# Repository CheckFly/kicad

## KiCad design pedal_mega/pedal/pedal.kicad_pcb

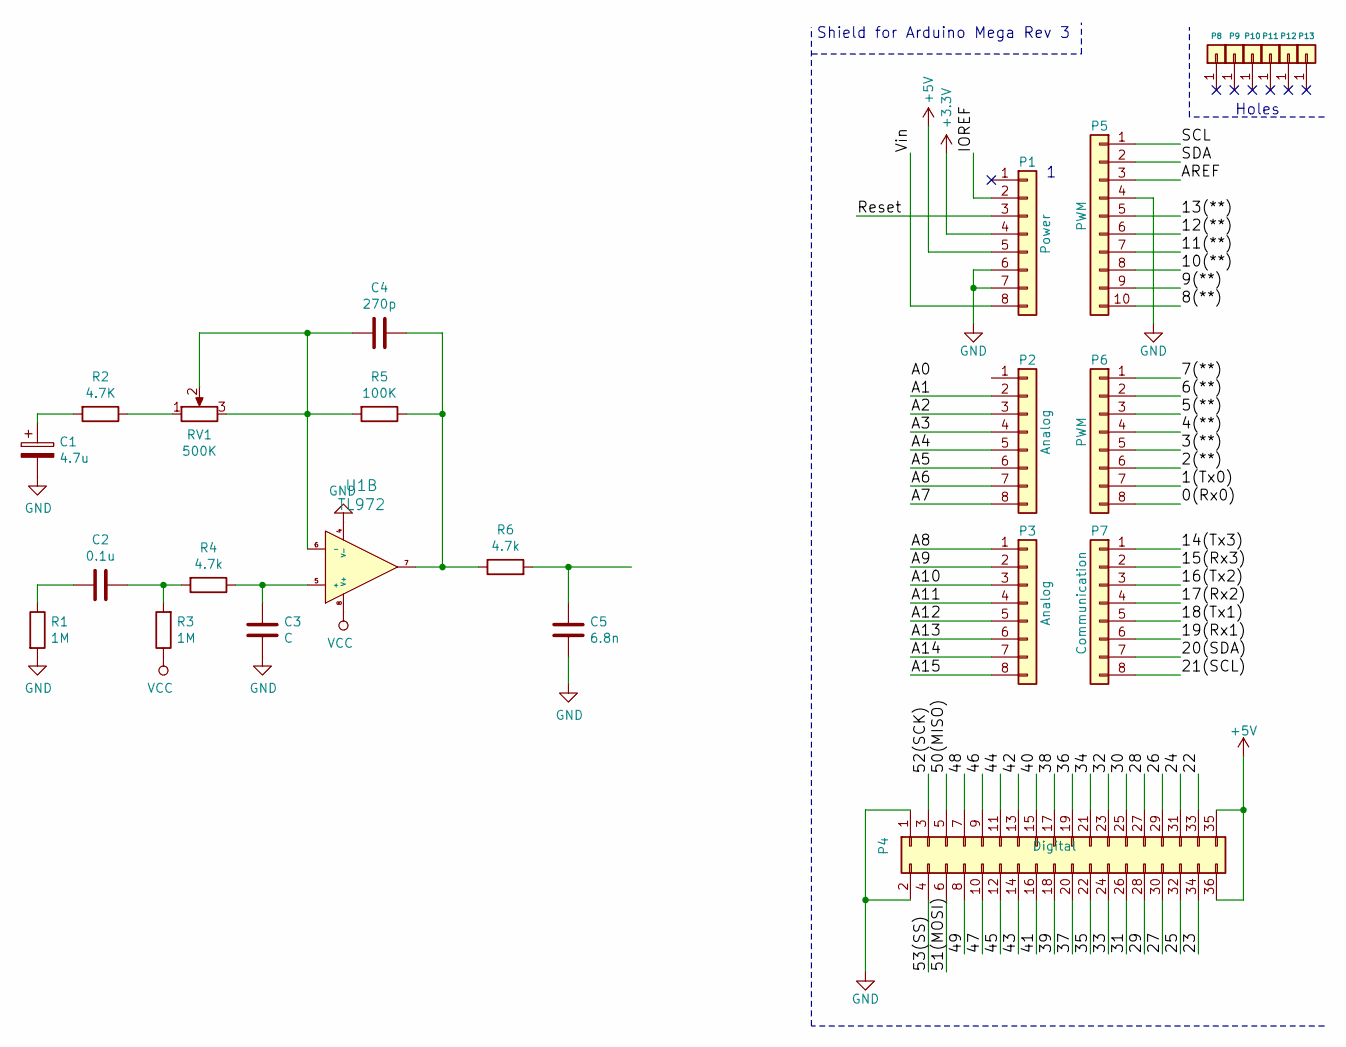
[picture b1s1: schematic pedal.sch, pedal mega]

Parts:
C1: 4.7u; CP_Radial_D10.0mm_P5.00mm
C2: 0.1u; C_Disc_D7.0mm_W2.5mm_P5.00mm
C3: C; C_Disc_D7.0mm_W2.5mm_P5.00mm
C4: 270p; CP_Radial_D10.0mm_P5.00mm
C5: 6.8n; CP_Radial_D10.0mm_P5.00mm
P1: Power; Socket_Strip_Arduino_1x08
P2, P3: Analog; Socket_Strip_Arduino_1x08
P4: Digital; Socket_Strip_Arduino_2x18
P5: PWM; Socket_Strip_Arduino_1x10
P6: PWM; Socket_Strip_Arduino_1x08
P7: Communication; Socket_Strip_Arduino_1x08
P8, P9, P10, P11, P12, P13: CONN_01X01; Arduino_1pin
R1, R3: 1M; R_Axial_DIN0207_L6.3mm_D2.5mm_P10.16mm_Horizontal
R2: 4.7K; R_Axial_DIN0207_L6.3mm_D2.5mm_P10.16mm_Horizontal
R4, R6: 4.7k; R_Axial_DIN0207_L6.3mm_D2.5mm_P10.16mm_Horizontal
R5: 100K; R_Axial_DIN0207_L6.3mm_D2.5mm_P10.16mm_Horizontal
RV1: 500K; Potentiometer_Vishay_T73YP_Vertical
U1: TL972; DIP-8_W7.62mm

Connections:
+3V3: P1.4
+5V: P1.5, P4.35, P4.36
/0(Rx0): P6.8
/1(Tx0): P6.7
/2(**): P6.6
/3(**): P6.5
/4(**): P6.4
/5(**): P6.3
/6(**): P6.2
/7(**): P6.1
/8(**): P5.10
/9(**): P5.9
/10(**): P5.8
/11(**): P5.7
/12(**): P5.6
/13(**): P5.5
/14(Tx3): P7.1
/15(Rx3): P7.2
/16(Tx2): P7.3
/17(Rx2): P7.4
/18(Tx1): P7.5
/19(Rx1): P7.6
/20(SDA): P7.7
/21(SCL): P7.8
/22: P4.33
/23: P4.34
/24: P4.31
/25: P4.32
/26: P4.29
/27: P4.30
/28: P4.27
/29: P4.28
/30: P4.25
/31: P4.26
/32: P4.23
/33: P4.24
/34: P4.21
/35: P4.22
/36: P4.19
/37: P4.20
/38: P4.17
/39: P4.18
/40: P4.15
/41: P4.16
/42: P4.13
/43: P4.14
/44: P4.11
/45: P4.12
/46: P4.9
/47: P4.10
/48: P4.7
/49: P4.8
/50(MISO): P4.5
/51(MOSI): P4.6
/52(SCK): P4.3
/53(SS): P4.4
/A1: P2.2
/A2: P2.3
/A3: P2.4
/A4: P2.5
/A5: P2.6
/A6: P2.7
/A7: P2.8
/A8: P3.1
/A9: P3.2
/A10: P3.3
/A11: P3.4
/A12: P3.5
/A13: P3.6
/A14: P3.7
/A15: P3.8
/AREF: P5.3
/IOREF: P1.2
/Reset: P1.3
/SCL: P5.1
/SDA: P5.2
/Vin: P1.8
GND: C1.2, C3.2, C5.2, P1.6, P1.7, P4.1, P4.2, P5.4, R1.2, U1.4 (V-)
unnamed: C1.1, R2.2
unnamed: C2.1, R3.2, R4.2
unnamed: C2.2, R1.1
unnamed: C3.1, R4.1, U1.5 (+)
unnamed: C4.1, R5.1, R6.1, U1.7
unnamed: C4.2, R5.2, RV1.2, RV1.3, U1.6 (-)
unnamed: C5.1, R6.2
unnamed: R2.1, RV1.1
VCC: R3.1, U1.8 (V+)

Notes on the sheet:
Shield for Arduino Mega Rev 3
Holes

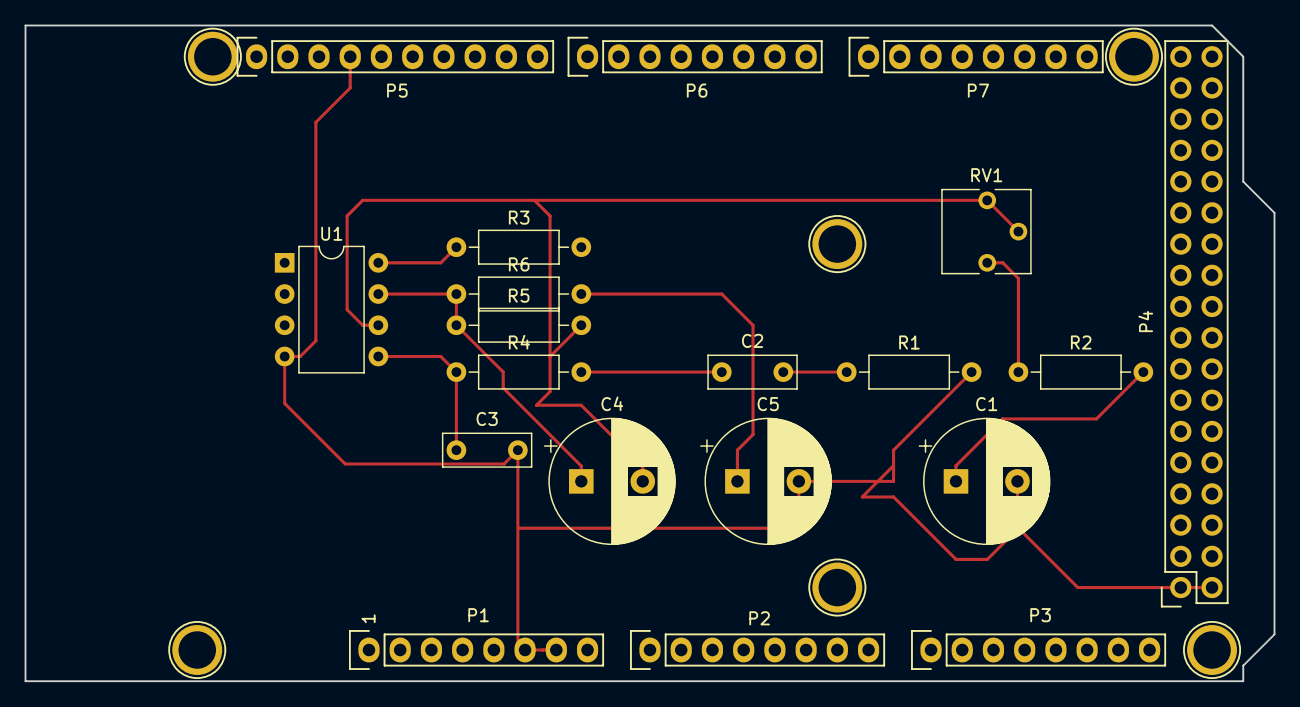
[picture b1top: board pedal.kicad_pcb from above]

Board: 2 copper layers, 101.6 x 53.3 mm, 26 parts (0 on the bottom side), 11 nets.

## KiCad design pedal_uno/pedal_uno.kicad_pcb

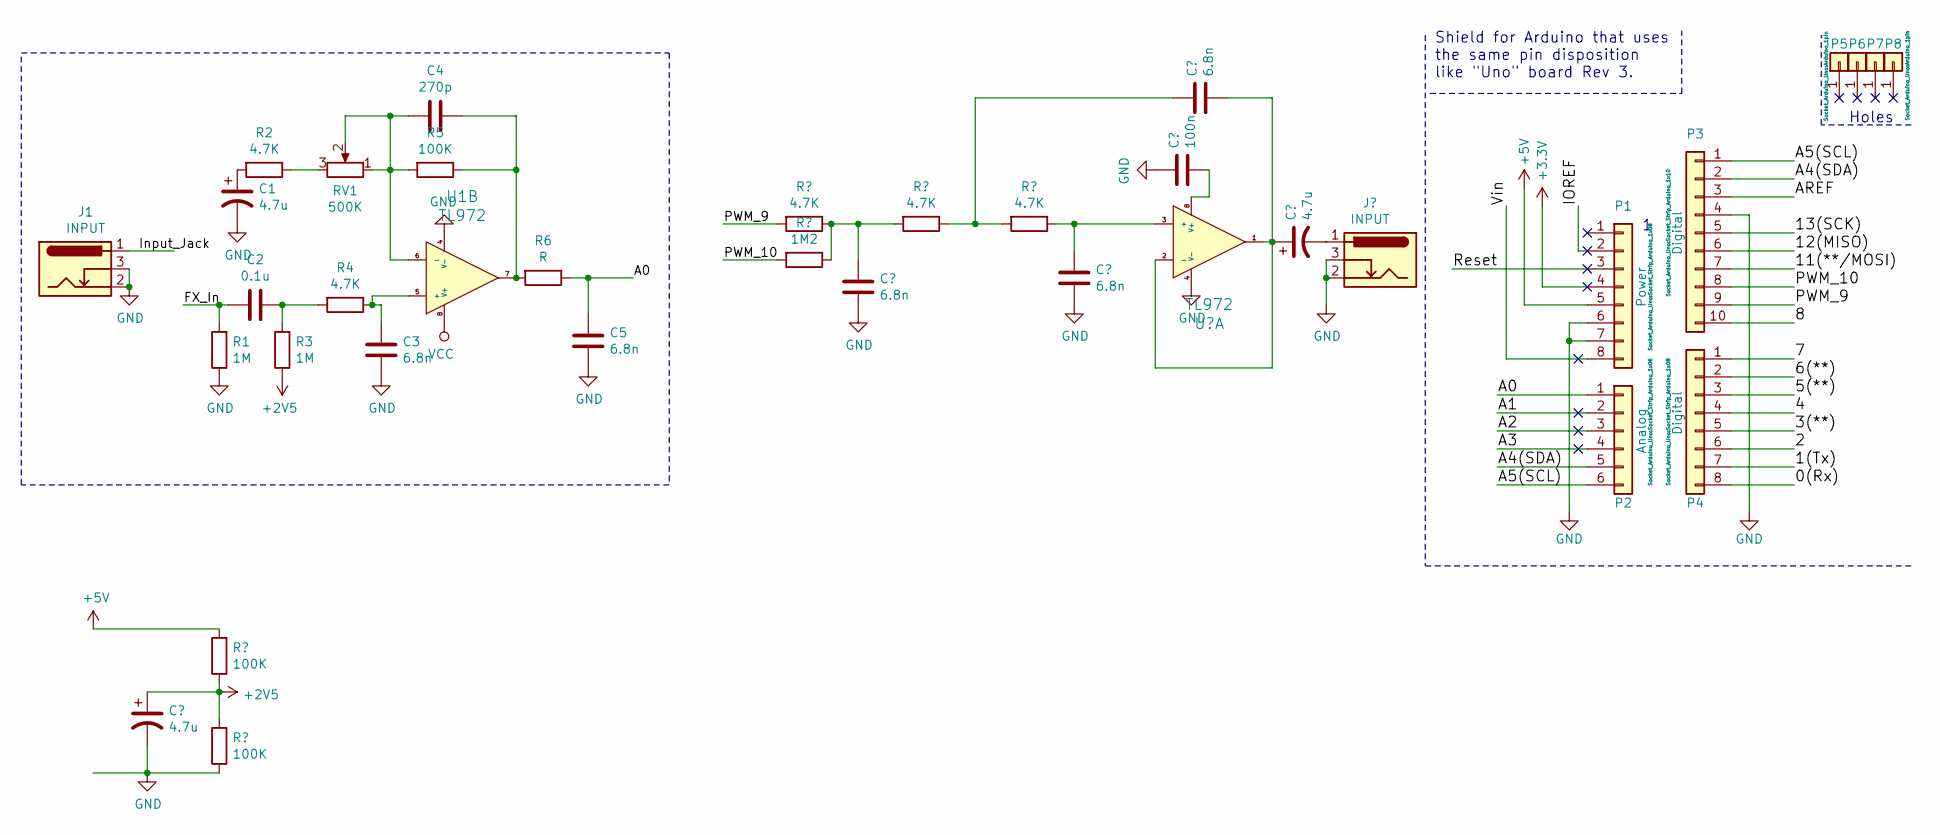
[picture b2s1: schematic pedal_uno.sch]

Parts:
C1: 4.7u; CP_Radial_D4.0mm_P2.00mm
C2: 0.1u; C_Axial_L5.1mm_D3.1mm_P10.00mm_Horizontal
C3, C5: 6.8n; C_Axial_L5.1mm_D3.1mm_P10.00mm_Horizontal
C4: 270p; C_Axial_L5.1mm_D3.1mm_P10.00mm_Horizontal
J1: INPUT; Jack_3.5mm_Neutrik_NMJ6HCD2_Horizontal
P1: Power; Socket_Strip_Arduino_1x08
P2: Analog; Socket_Strip_Arduino_1x06
P3: Digital; Socket_Strip_Arduino_1x10
P4: Digital; Socket_Strip_Arduino_1x08
P5, P6, P7, P8: CONN_01X01; Arduino_1pin
R1, R3: 1M; R_Axial_DIN0207_L6.3mm_D2.5mm_P10.16mm_Horizontal
R2, R4: 4.7K; R_Axial_DIN0207_L6.3mm_D2.5mm_P10.16mm_Horizontal
R5: 100K; R_Axial_DIN0207_L6.3mm_D2.5mm_P10.16mm_Horizontal
R6: R; R_Axial_DIN0207_L6.3mm_D2.5mm_P10.16mm_Horizontal
RV1: 500K; Potentiometer_Bourns_3386C_Horizontal
U1: TL972; DIP-8_W7.62mm_LongPads

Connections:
+2V5: R3.1
+3V3: P1.4
+5V: P1.5
/0(Rx): P4.8
/1(Tx): P4.7
/2: P4.6
/3(**): P4.5
/4: P4.4
/5(**): P4.3
/6(**): P4.2
/7: P4.1
/8: P3.10
/9(**): P3.9
/10(**/SS): P3.8
/11(**/MOSI): P3.7
/12(MISO): P3.6
/13(SCK): P3.5
/A0: C5.2, P2.1, R6.1
/A1: P2.2
/A2: P2.3
/A3: P2.4
/A4(SDA): P2.5, P3.2
/A5(SCL): P2.6, P3.1
/AREF: P3.3
/FX_In: C2.2, R1.2
/IOREF: P1.2
/Input_Jack: J1.1
/Reset: P1.3
/Vin: P1.8
GND: C1.2, C3.1, C5.1, J1.2, J1.3, P1.6, P1.7, P3.4, R1.1, U1.4 (V-)
unnamed: C1.1, R2.2
unnamed: C2.1, R3.2, R4.2
unnamed: C3.2, R4.1, U1.5 (+)
unnamed: C4.1, R5.1, R6.2, U1.7
unnamed: C4.2, R5.2, RV1.1, RV1.2, U1.6 (-)
unnamed: R2.1, RV1.3
VCC: U1.8 (V+)

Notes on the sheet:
Holes
Shield for Arduino that uses the same pin disposition like "Uno" board Rev 3.

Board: 2 copper layers, 22 parts (0 on the bottom side), 11 nets, no tracks yet.

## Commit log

2019-10-20 init
2019-10-23 power
